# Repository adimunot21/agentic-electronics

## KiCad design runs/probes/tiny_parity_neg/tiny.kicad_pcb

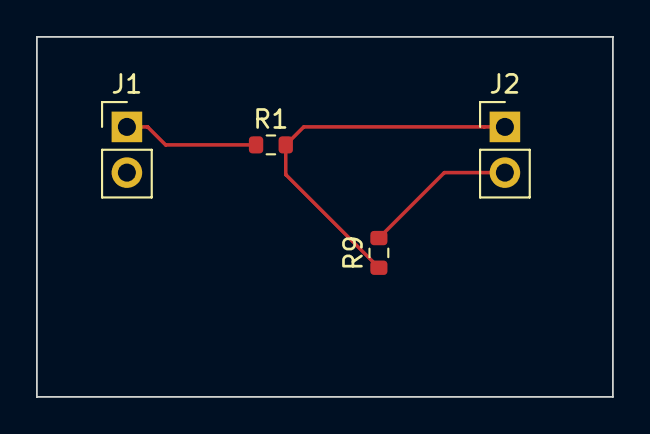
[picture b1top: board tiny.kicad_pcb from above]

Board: 2 copper layers, 32.0 x 20.0 mm, 4 parts (0 on the bottom side), 3 nets.

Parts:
J1: VIN_IN; PinHeader_1x02_P2.54mm_Vertical
J2: MID_OUT; PinHeader_1x02_P2.54mm_Vertical
R1, R9: 10k; R_0603_1608Metric

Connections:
/MID: J2.1, R1.2, R9.1
/VIN: J1.1, R1.1
GND: J1.2, J2.2, R9.2

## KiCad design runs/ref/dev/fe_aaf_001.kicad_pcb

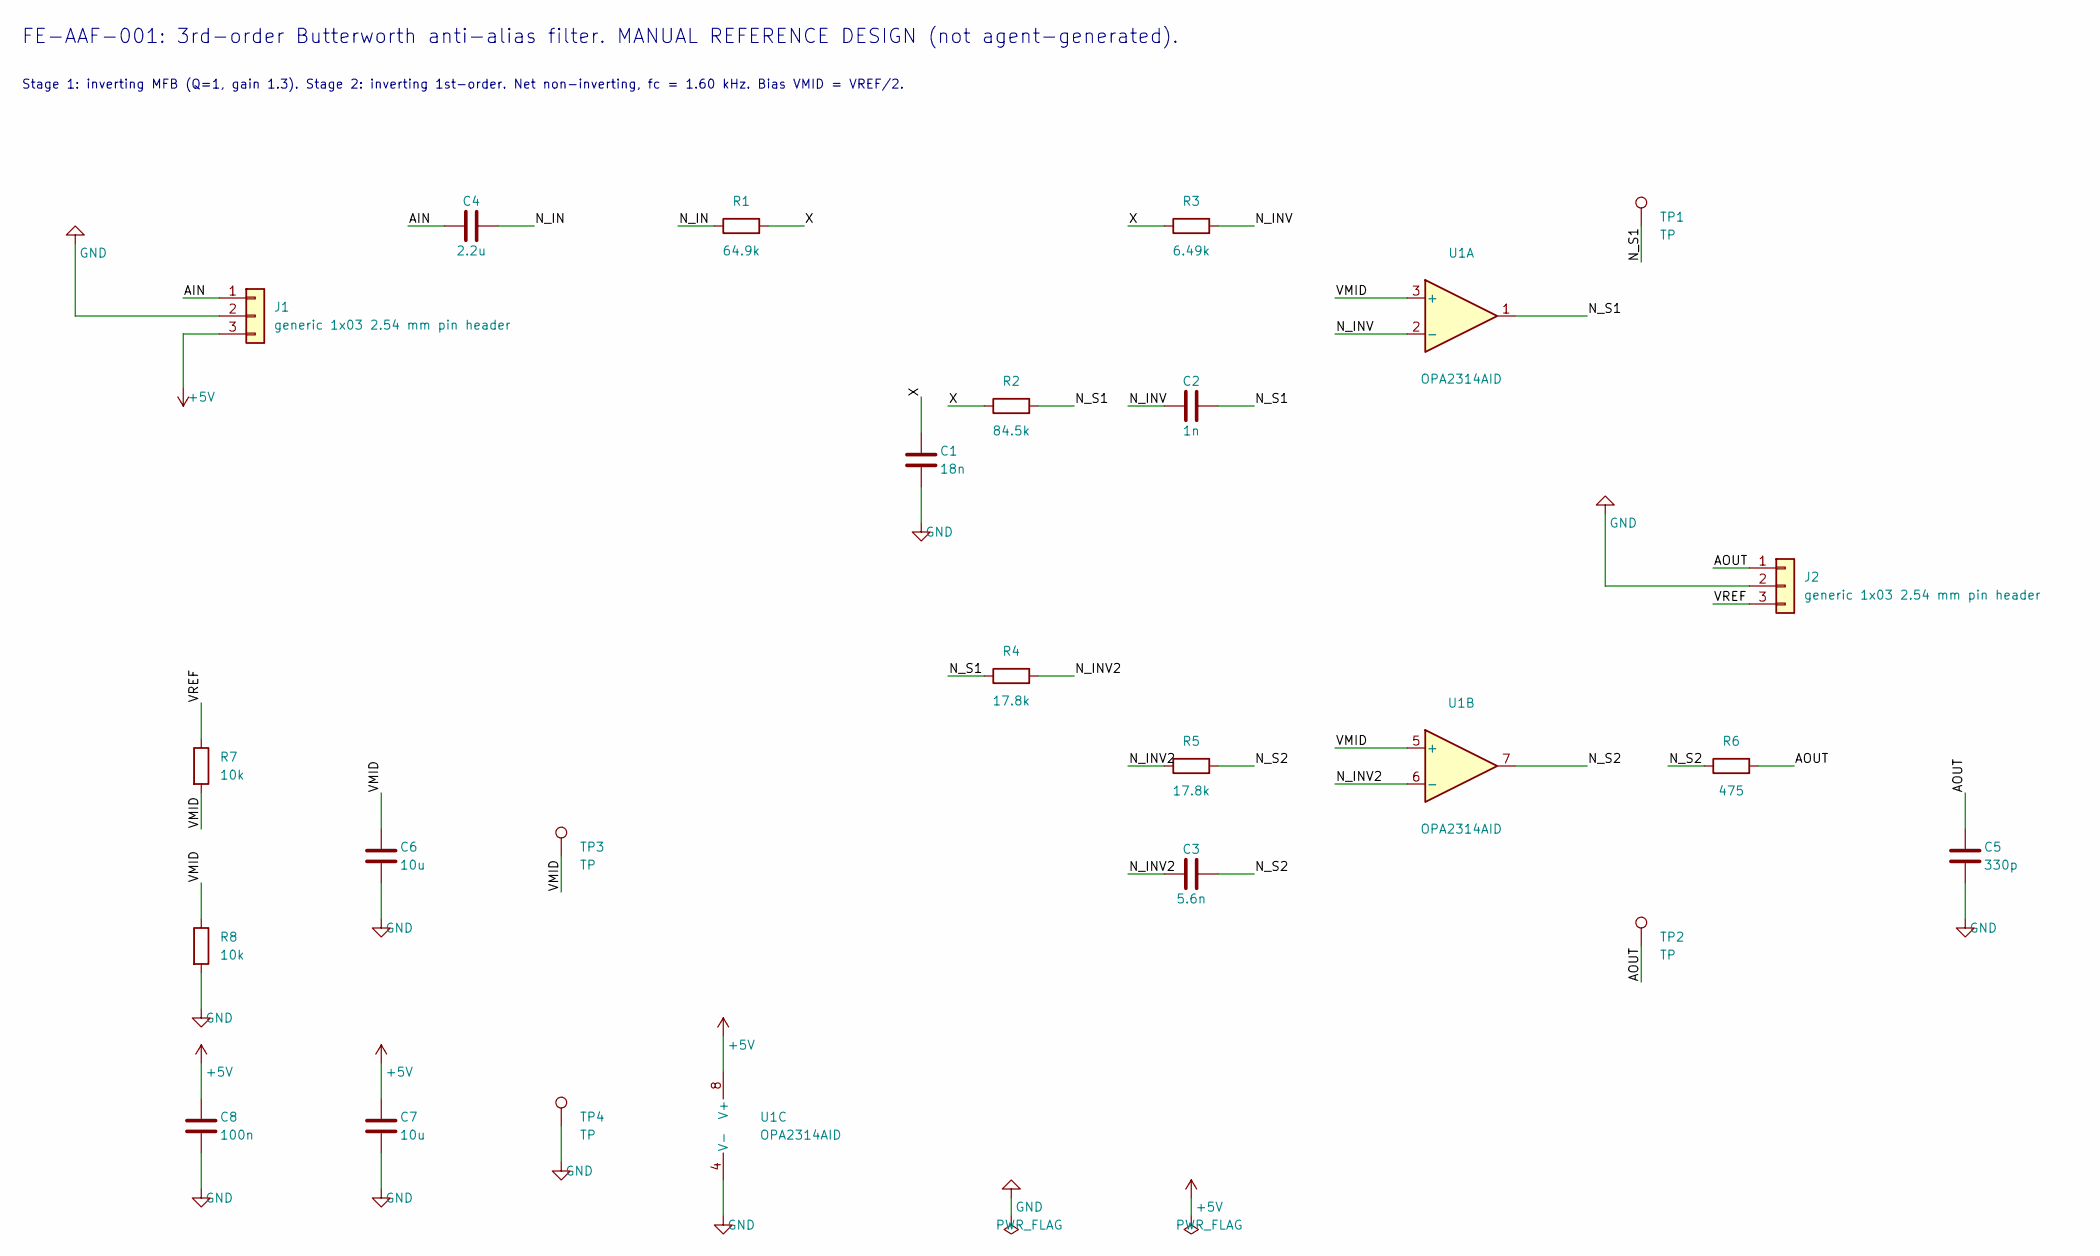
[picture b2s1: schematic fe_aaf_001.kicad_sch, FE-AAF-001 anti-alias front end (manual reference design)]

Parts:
C1: 18n; C_0805_2012Metric; MPN C0805C183J5GACTU
C2: 1n; C_0805_2012Metric; MPN C0805C102J5GACTU
C3: 5.6n; C_0805_2012Metric; MPN C0805C562J5GACTU
C4: 2.2u; C_1206_3216Metric; MPN C1206C225K4RACTU
C5: 330p; C_0805_2012Metric; MPN C0805C331J5GACTU
C6, C7: 10u; C_1206_3216Metric; MPN unselected
C8: 100n; C_0603_1608Metric; MPN unselected
J1, J2: generic 1x03 2.54 mm pin header; PinHeader_1x03_P2.54mm_Vertical; MPN generic 1x03 2.54 mm pin header
R1: 64.9k; R_0603_1608Metric; MPN RC0603FR-0764K9L
R2: 84.5k; R_0603_1608Metric; MPN RC0603FR-0784K5L
R3: 6.49k; R_0603_1608Metric; MPN RC0603FR-076K49L
R4, R5: 17.8k; R_0603_1608Metric; MPN RC0603FR-0717K8L
R6: 475; R_0603_1608Metric; MPN RC0603FR-07475RL
R7, R8: 10k; R_0603_1608Metric; MPN RT0603BRD0710KL
TP1, TP2, TP3, TP4: TP; TestPoint_Pad_D1.5mm; MPN no part (bare pad)
U1: OPA2314AID; SOIC-8_3.9x4.9mm_P1.27mm; MPN OPA2314AID

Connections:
+5V: C7.1, C8.1, J1.3, U1.8 (V+)
/AIN: C4.1, J1.1
/AOUT: C5.1, J2.1, R6.2, TP2.1
/N_IN: C4.2, R1.1
/N_INV: C2.1, R3.2, U1.2 (-)
/N_INV2: C3.1, R4.2, R5.1, U1.6 (-)
/N_S1: C2.2, R2.2, R4.1, TP1.1, U1.1
/N_S2: C3.2, R5.2, R6.1, U1.7
/VMID: C6.1, R7.2, R8.1, TP3.1, U1.3 (+), U1.5 (+)
/VREF: J2.3, R7.1
/X: C1.1, R1.2, R2.1, R3.1
GND: C1.2, C5.2, C6.2, C7.2, C8.2, J1.2, J2.2, R8.2, TP4.1, U1.4 (V-)

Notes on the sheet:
FE-AAF-001: 3rd-order Butterworth anti-alias filter. MANUAL REFERENCE DESIGN (not agent-generated).
Stage 1: inverting MFB (Q=1, gain 1.3). Stage 2: inverting 1st-order. Net non-inverting, fc = 1.60 kHz. Bias VMID = VREF/2.

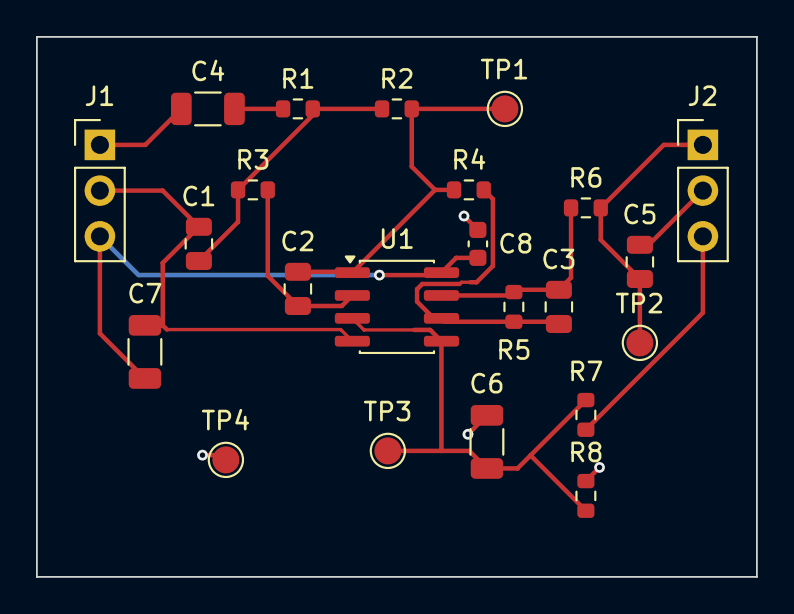
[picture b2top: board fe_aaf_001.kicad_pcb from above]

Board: 2 copper layers, 40.0 x 30.0 mm, 23 parts (0 on the bottom side), 12 nets.
